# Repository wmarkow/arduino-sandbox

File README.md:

# arduino-sandbox
Arduino sandbox for my projects

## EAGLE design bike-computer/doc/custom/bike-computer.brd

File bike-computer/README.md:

# A bike computer project

## Library dependencies

The following libraries are used in this project:

| Name | Version | Link |
| ---- | ---- | ----|
|Arduino Pro Mini 5V 328P|1.8.3|https://github.com/arduino/ArduinoCore-avr/|
|wmarkow modified Adafruit GFX Library|1.10.7|https://github.com/wmarkow/Adafruit-GFX-Library/tree/1.10.7-text-size|
|Adafruit SSD1306|2.4.5|https://github.com/adafruit/Adafruit_SSD1306|
|Adafruit BusIO|1.7.3|https://github.com/adafruit/Adafruit_BusIO|
|Array|1.0|https://github.com/wmarkow/arduino-array|
|Terminal|1.0|https://github.com/wmarkow/arduino-terminal|
|PinChangeInterrupt|1.2.9|https://github.com/NicoHood/PinChangeInterrupt|
|SPI|1.0|http://www.arduino.cc/en/Reference/SPI|
|Wire||https://github.com/arduino/ArduinoCore-avr/tree/master/libraries/Wire|
|EEPROM||https://github.com/arduino/ArduinoCore-avr/tree/master/libraries/EEPROM|

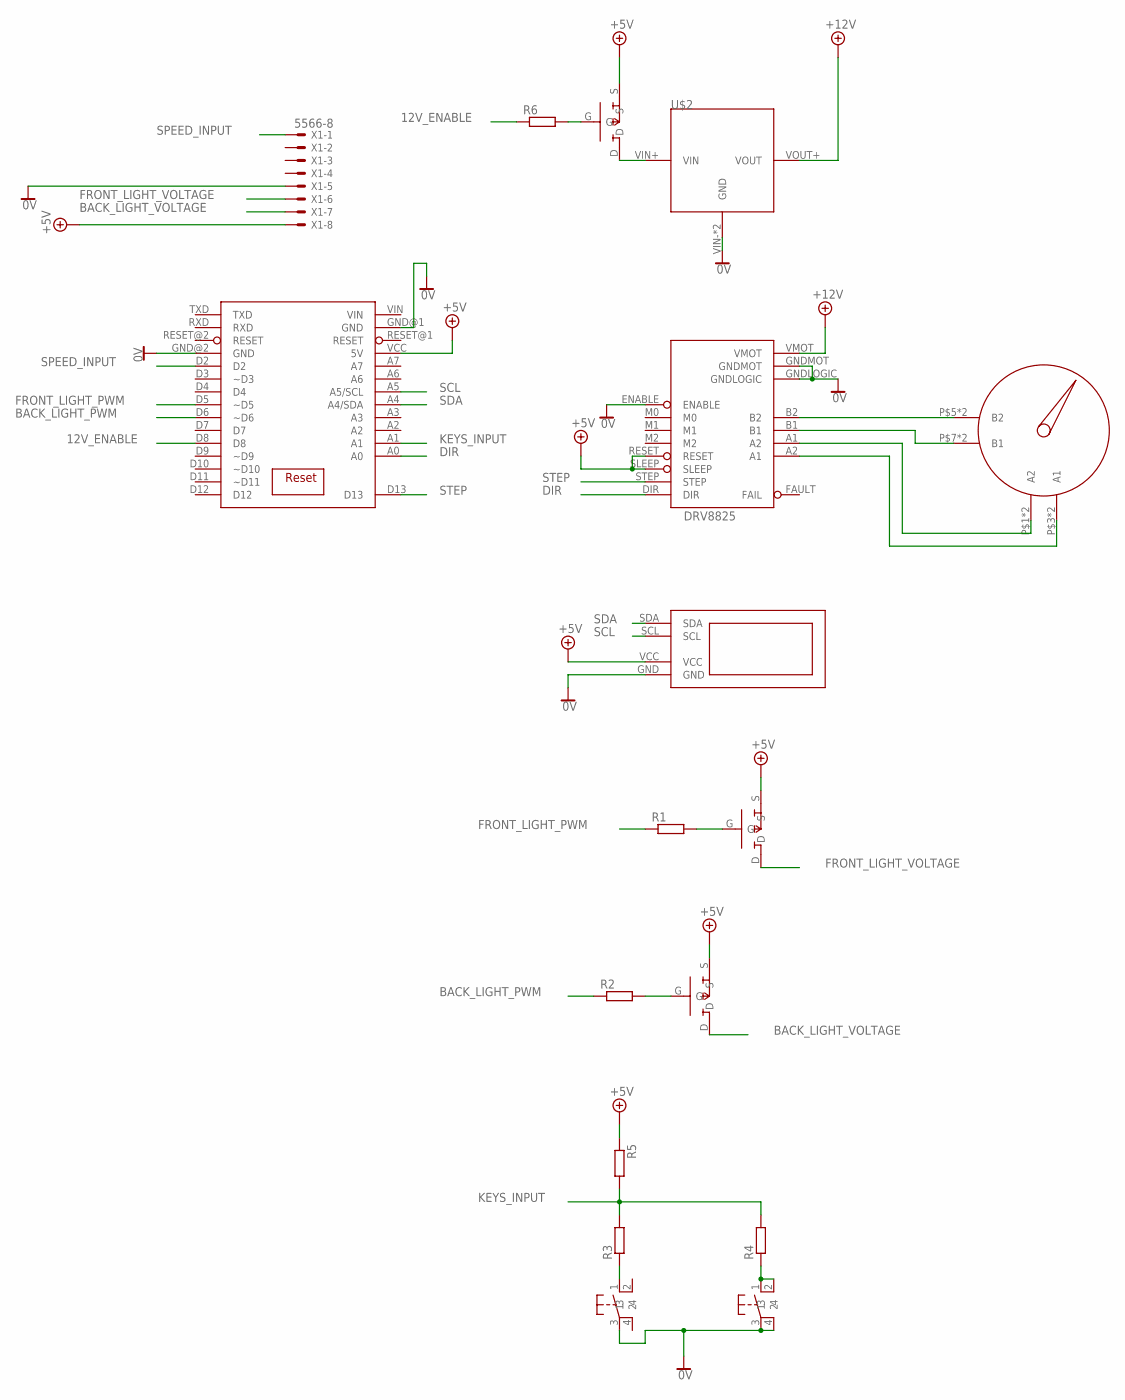
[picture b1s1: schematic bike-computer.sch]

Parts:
DRV8825: DRV8825_BOARD; DRV8255_BOARD
R1: R-EU_0617/17; 0617/17
R2, R6: R-EU_0207/15; 0207/15
R3: R-EU_0207/12; 0207/12
R4, R5: R-EU_0204/5; 0204/5
U$1: STEPPER_GAUGE
U$2: STEP_UP_REG
U$3: OLED_0.9
U$4, U$5, U$6: BS250; TO92(2.54)
U$7: ARDUINO_PRO_MINI
U$8, U$9: MICRO_SWITCH
X1: 5566-8

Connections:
0V: DRV8825.ENABLE, DRV8825.GNDLOGIC, DRV8825.GNDMOT, U$2.VIN- (GND), U$2.VOUT- (GND), U$3.GND, U$7.GND@1 (GND), U$7.GND@2 (GND), U$8.3, U$9.3, U$9.4, X1.5
12V_ENABLE: R6.1, U$7.D8
+5V: DRV8825.RESET, DRV8825.SLEEP, R5.1, U$3.VCC, U$4.S, U$5.S, U$6.S, U$7.VCC (5V), X1.8
+12V: DRV8825.VMOT, U$2.VOUT+ (VOUT)
BACK_LIGHT_PWM: R2.1, U$7.D6 (~D6)
BACK_LIGHT_VOLTAGE: U$5.D, X1.7
DIR: DRV8825.DIR, U$7.A0
FRONT_LIGHT_PWM: R1.1, U$7.D5 (~D5)
FRONT_LIGHT_VOLTAGE: U$4.D, X1.6
KEYS_INPUT: R3.2, R4.2, R5.2, U$7.A1
unnamed: DRV8825.B2, U$1.P$5 (B2), U$1.P$6 (B2)
unnamed: DRV8825.B1, U$1.P$7 (B1), U$1.P$8 (B1)
unnamed: DRV8825.A1 (A2), U$1.P$1 (A2), U$1.P$2 (A2)
unnamed: DRV8825.A2 (A1), U$1.P$3 (A1), U$1.P$4 (A1)
unnamed: R1.2, U$4.G
unnamed: R6.2, U$6.G
unnamed: U$2.VIN+ (VIN), U$6.D
unnamed: R2.2, U$5.G
unnamed: R3.1, U$8.1
unnamed: R4.1, U$9.1, U$9.2
SCL: U$3.SCL, U$7.A5 (A5/SCL)
SDA: U$3.SDA, U$7.A4 (A4/SDA)
SPEED_INPUT: U$7.D2, X1.1
STEP: DRV8825.STEP, U$7.D13

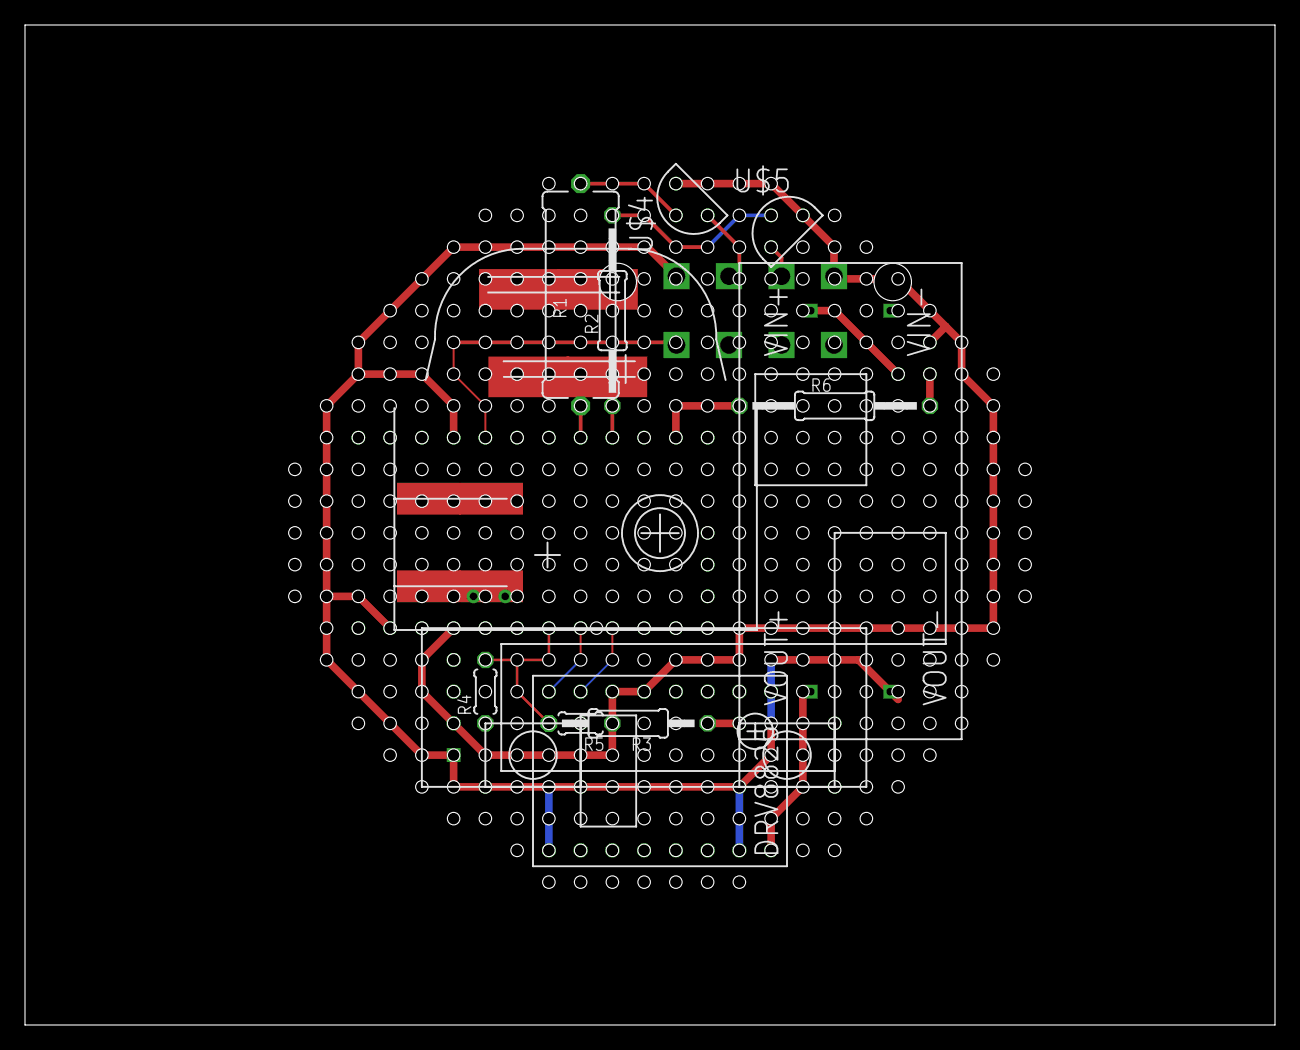
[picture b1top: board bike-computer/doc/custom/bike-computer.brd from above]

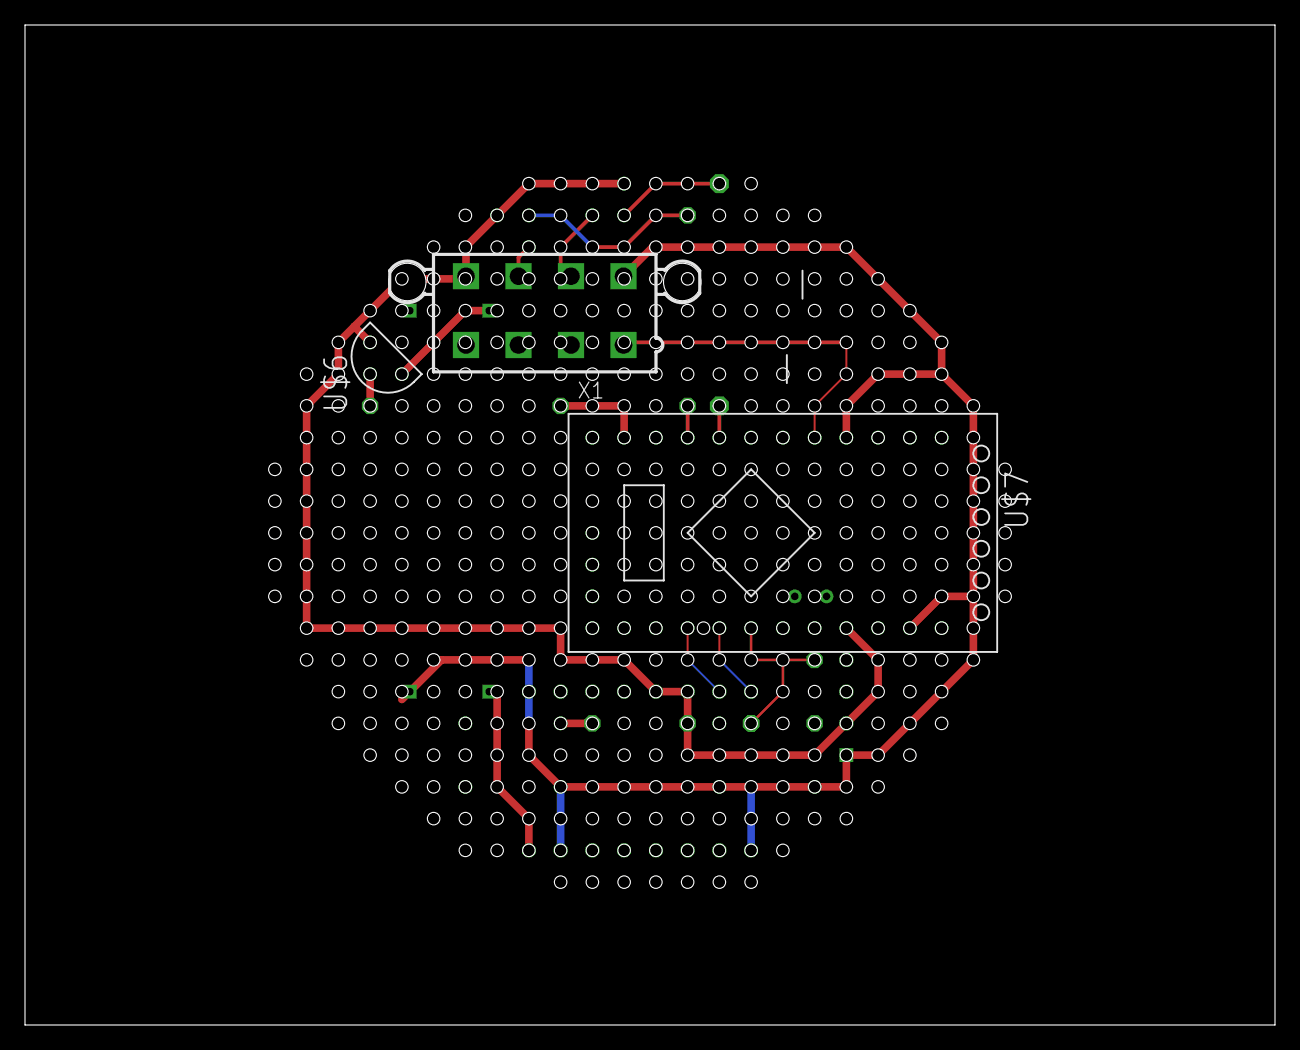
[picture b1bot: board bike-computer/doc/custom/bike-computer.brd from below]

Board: 2 copper layers, 100.0 x 80.0 mm, 17 parts (3 on the bottom side), 24 nets.

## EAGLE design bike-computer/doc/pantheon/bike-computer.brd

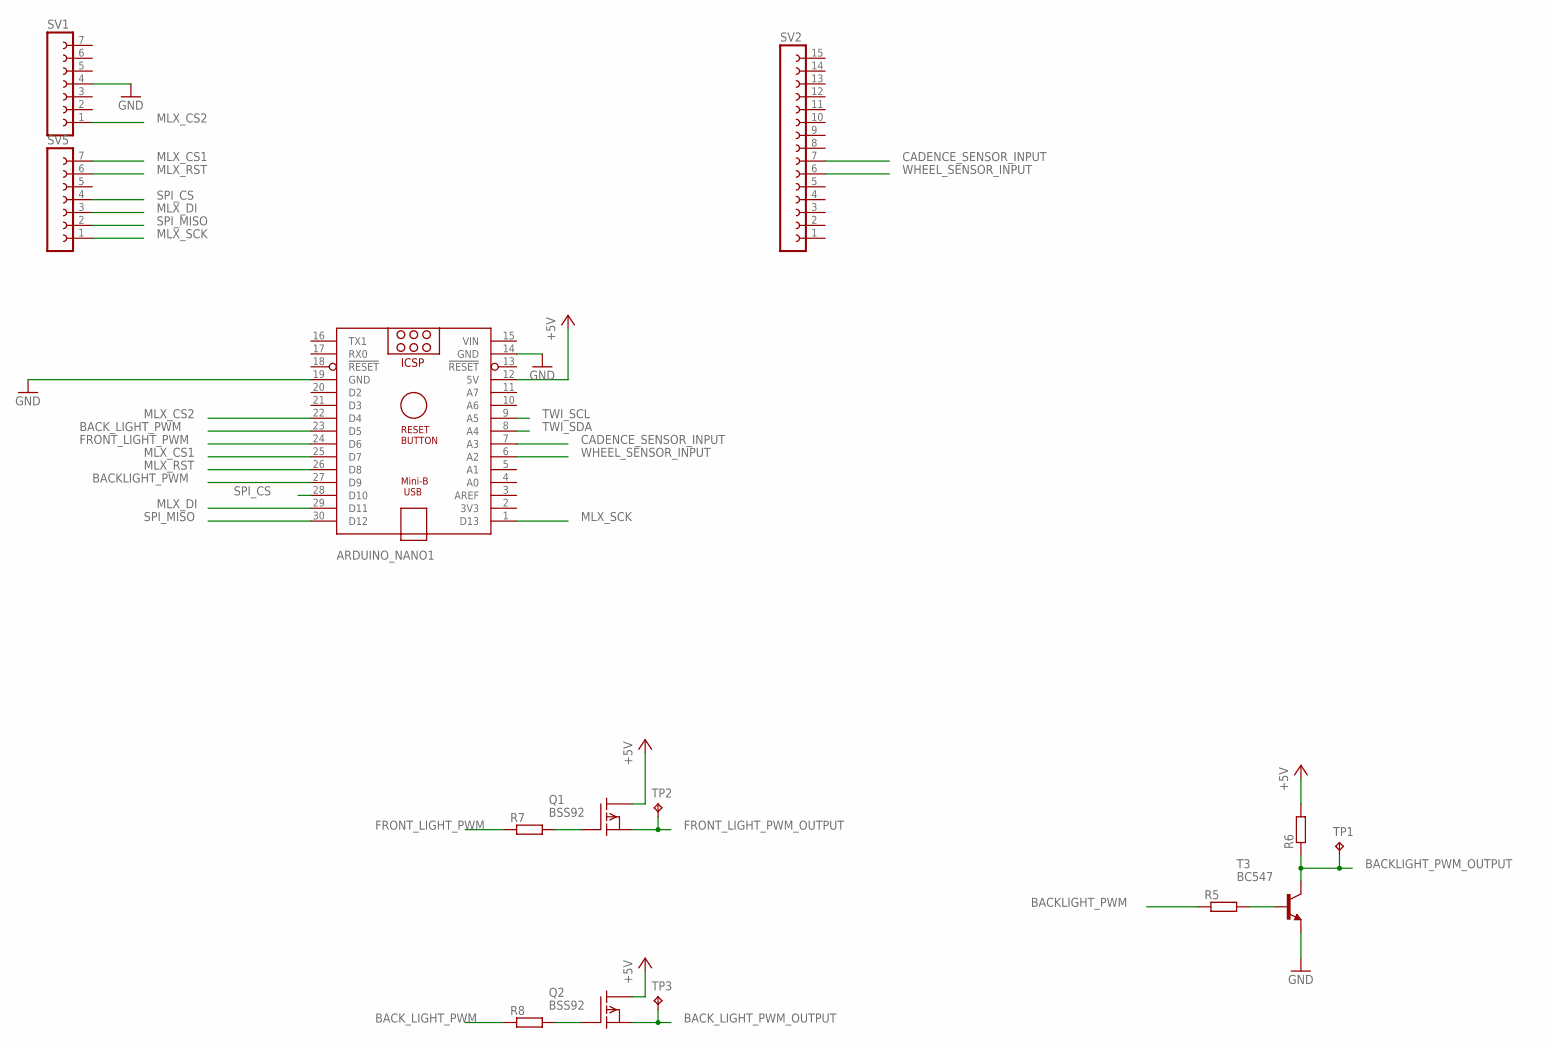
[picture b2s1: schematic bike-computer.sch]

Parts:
ARDUINO_NANO1: ARDUINO_NANO
Q1, Q2: BSS92; TO92
R5, R7, R8: R-EU_0204/5; 0204/5
R6: R-EU_0207/10; 0207/10
SV1, SV5: FE07-1; FE07
SV2: FE15-1; FE15
T3: BC547; TO92
TP1, TP2, TP3: TPPAD1-13; P1-13

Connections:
+5V: ARDUINO_NANO1.12 (5V), Q1.2 (D), Q2.2 (D), R6.2
BACKLIGHT_PWM: ARDUINO_NANO1.27 (D9), R5.1
BACKLIGHT_PWM_OUTPUT: R6.1, T3.3 (C), TP1.TP
BACK_LIGHT_PWM: ARDUINO_NANO1.23 (D5), R8.1
BACK_LIGHT_PWM_OUTPUT: Q2.3 (S), TP3.TP
CADENCE_SENSOR_INPUT: ARDUINO_NANO1.7 (A3), SV2.7
FRONT_LIGHT_PWM: ARDUINO_NANO1.24 (D6), R7.1
FRONT_LIGHT_PWM_OUTPUT: Q1.3 (S), TP2.TP
GND: ARDUINO_NANO1.14 (GND), ARDUINO_NANO1.19 (GND), SV1.4, T3.1 (E)
MLX_CS1: ARDUINO_NANO1.25 (D7), SV5.7
MLX_CS2: ARDUINO_NANO1.22 (D4), SV1.1
MLX_DI: ARDUINO_NANO1.29 (D11), SV5.3
MLX_RST: ARDUINO_NANO1.26 (D8), SV5.6
MLX_SCK: ARDUINO_NANO1.1 (D13), SV5.1
unnamed: R5.2, T3.2 (B)
unnamed: Q1.1 (G), R7.2
unnamed: Q2.1 (G), R8.2
SPI_CS: ARDUINO_NANO1.28 (D10), SV5.4
SPI_MISO: ARDUINO_NANO1.30 (D12), SV5.2
TWI_SCL: ARDUINO_NANO1.9 (A5)
TWI_SDA: ARDUINO_NANO1.8 (A4)
VIN: ARDUINO_NANO1.15 (VIN)
WHEEL_SENSOR_INPUT: ARDUINO_NANO1.6 (A2), SV2.6

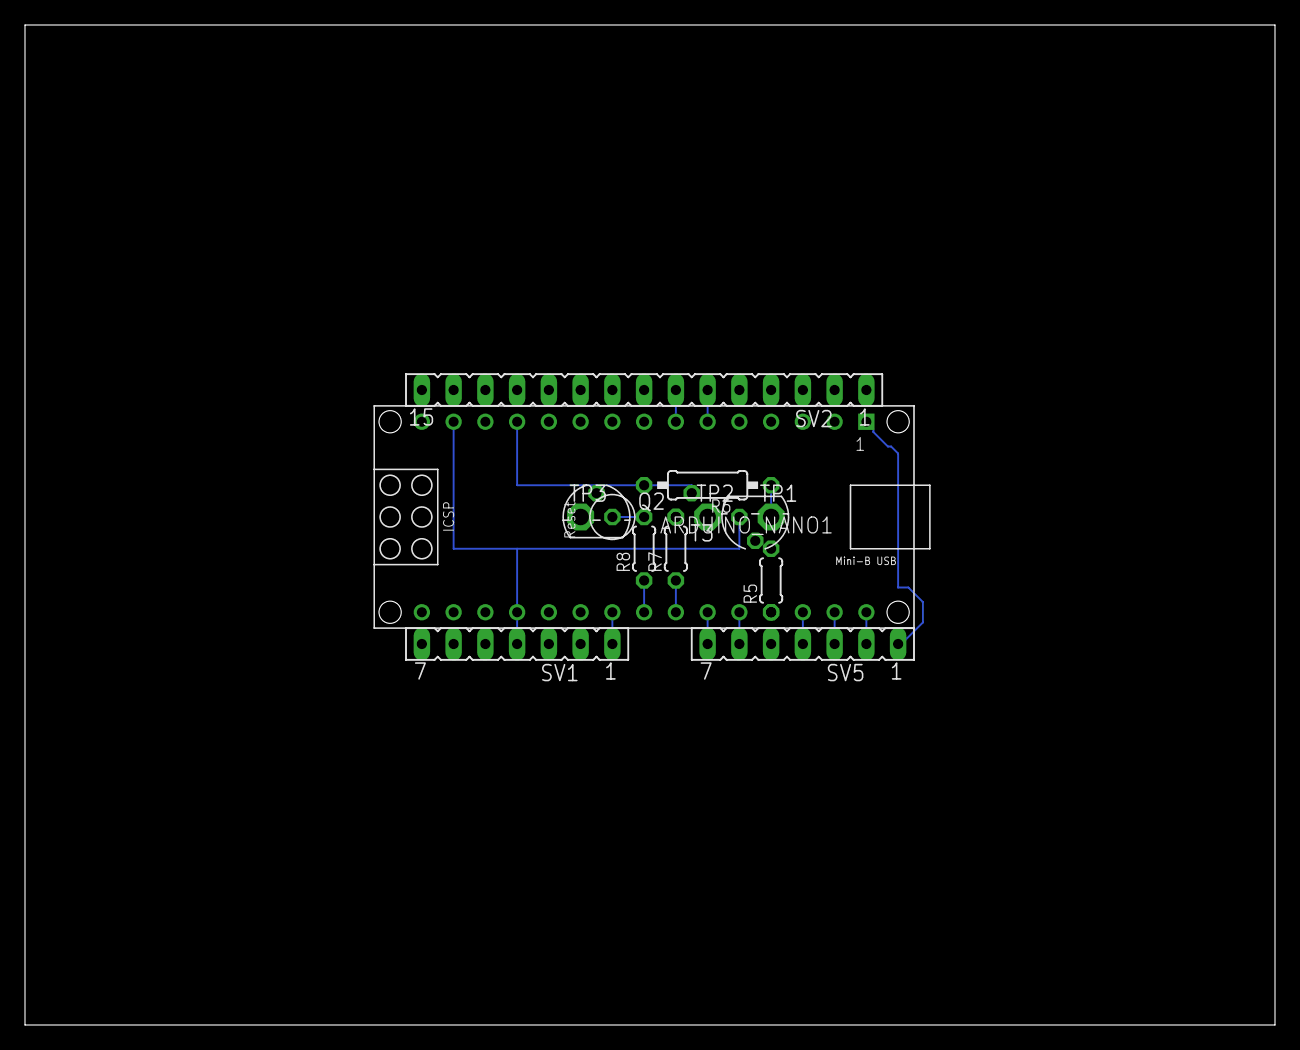
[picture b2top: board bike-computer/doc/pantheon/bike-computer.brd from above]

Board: 2 copper layers, 100.0 x 80.0 mm, 14 parts (1 on the bottom side), 20 nets.

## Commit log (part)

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2020-05-31 [Bike] Show a splaschscreen on the display when dashboard is in reset procedure.
2020-06-05 [Bike] Move speed event debug info to dashboard.
2020-06-06 [Bike] Show speed, acceleration and breaks status on the display.
2020-06-06 [DollHouse] Normalize sounds volume.
2020-06-07 [DollHouse] Refactor: introduce SD root folder, so it is easier to understand where to copy the files to SD card.
2020-06-09 [Bike] Rework speed and acceleration on the dashboard.
2020-06-11 [Bike] Set the wheel diameter to 28 inches
2020-09-30 [DollHouse] Add rooster sound. It must be at most 44.1kHz.
2020-11-20 [DollHouse] Improve gitignore
2020-11-29 [Trains] Add NimBLE-Arduino minimal example which works.
2020-11-29 [Trains] ServerCallbacks are important here otherwise BLE Scanner will not connect.
2020-12-03 [Trains] Initial version of Legoino Hub emulation. Basically it works; just need to add motor driver.
2020-12-03 [Trains] Make the PWM working smoothly for forward.
2020-12-22 [Welder] Rename the example so it is more compatible with Arduino IDE.
2020-12-22 [Trains] PoweredUp sends data to port B.
2020-12-24 [Welder] Add button suport.
2021-01-04 [Trains] Imrpove gitignore.
2021-01-04 [Welder] Refactor: introduce contnuous welding.
2021-01-04 [Welder] Go back to continuous welding mode.
2021-01-10 [SlowMotion] Improve gitignore.
2021-02-07 [SlowMotion] Update gitignore. Remove eclipse files from Git.
2021-02-08 [Distiller] Add basic code for water flow sensor. For me the RPM with value 8000 seems to be wrong.
2021-02-25 [Distiller] Move the water flow sensor code to its own class.
2021-02-25 [Distiller] Experiment: measure water specific heat capacity.
2021-02-26 [Distiller] Introduce DS18B20 wrapper class.
2021-04-21 [Distiller] Move to ESP32 DEVKIT V1 DOIT.
2021-04-21 [Distiller] Use RF24Log library for logging.
2021-04-22 [Distiller] Improvement in DS18B20 hardware failures.
2021-04-24 [Distiller] Add manufacturer data to adverising.
2021-05-07 [Distiller] Add system up time. [Distiller] Use latest RF24Log.
2021-05-23 [Bike] Display trip distance and total distance.
2021-05-23 [Bike] Add 'dash eeprom' command to dump EEPROM.
2021-05-23 [Bike] Improve dash display.
2021-05-25 [Bike] Display also text size on float text size demo.
2021-05-26 [Bike] Save data to EEPROM only when the spead goes back to 0.
2021-10-30 [Welder] Preparation to use potentiometer to control wire speed.
2021-11-21 [Distiller] Make thermometer resolution customizable.
2022-01-04 [Welder] Add PlatformIO support.
2022-01-04 Create LICENSE
2022-04-04 [Welder] Change serial speed to 115200.
2022-05-02 [Welder] Add CNC Shield pinout.
2022-06-30 [Iot] preliminary works on Iot example
2022-09-09 [Iot] Update platformio.ini
2022-09-09 [Iot] Update example of iot-example project.
2022-09-09 [Iot] Disable logging in transportDataAvailable() because it called very often.
2023-05-24 [FixHunting]Preliminary workable code for transmitter and receiver.
2023-05-25 [FoxHunting] Sending and receiving MOE morse signal.
2023-05-29 [FoxHunting] Allow for bit error rate during transmission, however it doesn't work.
2023-05-30 [FoxHunting] Lower air data rate to 5000bps to increase the range.
2023-06-11 [FoxHunting] Lower beep duration, so maybe it will be easier to hear the out-of-signal.
2023-06-18 [FocHunting] Make the transmission range smaller (for antena directivity tests).
2023-06-23 [FoxHunting] Experiments with HC-12 and various packets length.
2023-06-24 [FoxHunting] Beep when receiving data.
2023-06-25 [FoxHunting] Don't wait until packet really send (it will wait anyway later)
2023-06-25 [FoxHunting] Current range.
2023-06-25 [FoxHunting] Don't send headers.
2023-07-01 [FoxHunting] Add comments on the pictures.
2023-07-01 [FoxHunting] Schematics of FS1000A.
2023-07-01 [FoxHunting] Move range images of HC12 to a different folder.
2023-07-02 [FoxHunting] Printing to serial may influence the reception routines.
2023-07-10 [FoxHunting] Reduce air speed to 1200 bps.
2023-07-10 [FoxHunting] Meassure RSSI from the rssi voltage. It doesn't work nice.
2023-07-11 [FoxHunting] Make a beep with different frequencies to indicate RSPI drop.
2023-07-19 [FoxHunting] Add range image.
2023-07-21 [FoxHunting] A better way to receive preamble.
2023-07-31 [FoxHunting] Constantly meassure RSSI. Bugfix.
2023-08-14 [FoxHunting] Meassure RSSI voltage.
    Speed is 2400 bps
    Receiving preamble 0b101010101010
    Voltage pulsation around 250mV (number between 335 and 395 where 1023 is 5.0V)
2023-09-03 [FoxHunting] Change the way of meassuring RSSI;fluctuations are now around 10 (per 1023).
2023-09-11 [FoxHunting] Receive preamble with some errors accepted. Add RSSI meassurement graphs.
2023-09-25 [FoxHunting] Add HC-12 documentation.
2023-10-01 [FoxHunting] Another range tests.
    Chart created with Plotly https://chart-studio.plotly.com/create/#/
2023-10-11 [STLINKV2] Add more images about steps how to unlock the device.
2023-10-11 [STLINKV2] Fix readme.
2023-10-11 [STLINKV2] Doc about SWIM protocol.
2023-10-14 [FoxHunting] Add some docs.
2023-10-16 [FoxHuting] Rebane the doc.
2023-10-16 [FoxHunting] Small refactor: check the chip before sending command.
2023-10-19 [FoxHunting] Rework API so it is possible to apply default chip config. [FoxHunting] Add default config.
2023-10-20 [FoxHunting] Configure CW transmission mode.
2023-10-22 [FoxHunting] Add html documentation for Si4xxx chips.
2023-10-22 [FoxHunting] Refactor: move fake F3E code its own files.
2023-10-22 [FoxHunting] Refactor: move CW to its own files. [FoxHunting] Create CWTransmitter example.
    CW doesn't work with PMR 446 FM receiver. Nothing hear in the loudspeaker. Probably because there is no FM modulation when sending CW.
2024-01-05 [FoxHunting] Mor docs about Si443x
2024-01-14 [FoxHunting] Preliminary work on sending commands.
2024-01-14 [FoxHunting] Make the names more C-like style.
2024-01-16 [FoxHunting] Add terminal to CWTransmiter example
2024-01-16 [FoxHunting] Bugfix in MODEM_MOD_TYPE property address.
2024-01-21 [FoxHunting] Mode the code to an intermediate library subroject.
    Platformio will compile it into a LIB file an SDCC compiler can not link unused functions:
    https://sourceforge.net/p/sdcc/discussion/1865/thread/05f487b4/#d6c6/6264
2024-01-21 [FoxHunting] Display device info in a separate compilation unit. Flash usage 98.9%.
2024-02-19 [FoxHunting] Some work on CW.
2024-02-25 [FoxHunting] Example of OOK modulation.
2024-02-25 [FoxHunting] GPIO0 pull up enabled. It generates strong CW signal.
2024-02-25 [FoxHunting] Put more comments in CW example about how it works.
2024-03-13 [FoxHunting] Add 2FSK example hearable on PMR 446.00625 MHz.
2024-03-13 [FoxHunting] Improve CW example.
2024-03-13 [FoxHunting] Make 2FSK example a default one (hearable on PMR with FM demodulation).
2024-05-01 [FoxHunting] Go back to the standard fox transmitter with 1000Hz tone over 2FSK.
2024-05-01 [FoxHunting] Make the fox signal longer.
2024-06-06 [FoxHunting] Change duration of OOK to 2 seconds to match the duration of Fake F3E example.
2024-06-06 [FoxHunting] Add -3dB spectrum width meassurements for different modulations.
2024-06-22 [FoxHunting] Define 10dBm power level.
2024-06-22 [FoxHunting] A simple markdown with current consumption measurements.
2024-06-22 [FoxHunting] Add simple MOE/MOI/MOS/MOH/MO5 fox FM transmitter.
2024-07-03 [FoxHunting] Embedding precalculated values also doesn't help: we have 100% of flash usage.
2024-07-03 [FoxHunting] Add possibility to transmit on specific channel.
2024-07-04 [FoxHunting] Add image about understanding WDS3 config_file and 2FSK spectrum.
    Corruntly the fox is hearable on FM 434.093750 MHz
2024-07-04 [FoxHunting] Preparations for different channels (as suggested by SP3IZN).
2024-07-07 [FoxHunting] Send test fake APRS frame (~200ms) similar to RS41 radiosonde.
2024-07-07 [FoxHunting] It seems to be working but the processor gets restarted after AWU wake up.
2024-07-09 [FoxHunting] Patch for framework issue #164 AWU_IRQHandler not working for STM8S
    https://github.com/tenbaht/sduino/issues/164 AWU_IRQHandler not working for STM8S
2024-07-10 [FoxHunting] Correct power consumption measurements.
2024-07-12 [FoxHunting] Refactor.
2024-07-12 [FoxHunting] Sending/silence with 500ms/500ms is more or less working nice on Quansheng's S-Meter with Egzumer.
2024-07-23 [FoxHunting] Preliminary work on RX CW mode.
    PB4 pin interrupt works but it is triggered evevn if there is no carrier.
2024-07-24 [FoxHunting] Preliminary algorithm: switching between RX and TX states with carrier presence.
2024-07-24 [FoxHunting] Move morse related code to its own files.
2024-07-25 [FoxHunting] Find the lowest possible RSSI threshold.
2024-07-31 [FoxHunting] Avergae RSSI seems to be more stable now.
2024-07-31 [FoxHunting] Calculate average RSSI faster.
2024-08-02 [FoxHunting] We don't need to RSSI threshold of SI4438
2024-08-04 [FoxHunting] Adjust the times a bit.
2024-08-04 [FoxHunting] Update RSSI treshold as often as possible.
2024-08-07 [FoxHunting] Expirmental change to doesn't react on random RSSI noise changes. Set RSSI treshold to 20. Meassure RSSI: 32 samples every 16ms (it takes, 32x16ms=512ms).
2024-08-07 [FoxHunting] Add RSSI calculation debug messages.
2024-08-07 [FoxHunting] Three tone beeper.
2024-08-10 [FoxHunting] Experimental change: calculate RSSI standard deviation.
2024-10-05 [FoxHunting] Calculate RSSI treshold based on current RSSI value and its standard deviation.
2024-10-05 [FoxHunting] Make the last round beeps faster, to indicate that it goes to sleep soon.
2024-10-06 [FoxHunting] Make dit duration to be calculated from WPM
2024-10-07 [FoxHunting] Refactor transmition cycle.
2024-10-07 [FoxHunting] Improve RSSI calculation by introducing a small delay after exiting sleep mode.
2024-10-19 [FoxHunting] Refactor CW modulation source code.
2024-10-19 [FoxHunting] Make OOKTransmitter compilable.
2024-10-19 [FoxHunting] Refactor FSK code.
2024-10-19 [FoxHunting] Rename fake_f3e files into fsk files.
2024-10-19 [FoxHunting] Refactor: move AFSK methods to their own file.
2024-10-19 [FoxHunting] Make all examples compilable.
2024-10-19 [FoxHunting] refactor AFSK APRS example.
2024-11-02 [IoT] The duration of micros() has impact to APRS tones; their frequencies are to low. Now it is a bit better, but not perfect.
2024-11-03 [IoT] Calculate FCS (Frame Check Sequence) and some minor fixes.
2024-11-03 [FoxHunting] Very important bugfix: bit shifting and assigning result back to the variable.
2024-11-06 [FoxHunting] Make it more according to AX.25 standard. Work in progress.
2024-11-11 [FoxHunting] Refactoring: this is a method without bit stuffing.
2024-11-12 [FoxHunting] This gets decoded in aprslib.
2024-11-13 [FoxHunting] Generate tones with the help of interrupt, which should be more stable.
2024-11-18 [FoxHunting] This little trick makes the signal gets decoded by aprslib.
    Transition between SPACE and MARK is better and the signal looks better.
2024-11-18 [FoxHunting] APRS101 documentation.
2024-11-29 [LCMeter] Add docs of VK3BHR LC meter project.
2024-11-29 [LCMeter] It uses 1000pC and 82uH but the generated frequency is too low.
2024-11-29 [FoxHunting] Send APRS on 432.500 MHz.
2024-11-29 [FoxHunting] Use WIDE2-1 hints for digipiters
2024-12-02 [FoxHunting] Put more comments and make the configuration easier.
2024-12-02 [LCMeter] Add Excel sheet with error's caclulation.
2024-12-02 [LCMeter] Add example with LM311; it works correct as on VK3BHR's pdf.
2024-12-02 [LCMeter] Rename the VK3BHR schematic example
2024-12-07 [FoxHunting] Rename the config name to indicate it is based on 434.100MHz
2024-12-07 [FoxHunting] Make the fox transmitter working on a correct channel with base of 432.500 MHz
2024-12-07 [FoxHunting] Make the transmission power easily configurable.
2024-12-24 [FoxHunting] refactoring: move songs to their own files.
2024-12-25 [FoxHunting] Add 'Final Countdown'.
2024-12-25 [FoxHunting] Add 'never gonna give you up'.
2024-12-25 [FoxHunting] Adopt 'Never gonna give you up'
2024-12-25 [FoxHunting] Adopt 'Final Countdown'
